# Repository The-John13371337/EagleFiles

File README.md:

# EagleFiles
This is a small Repo for cloning the malduino project files for the board design.
Seytonic didnt make this, i did because he refuses to upload the board schematics (although he is very busy)
Enjoy
Also btw im pretty sure that this board will work however look over the .sch and the sch preview so if somthing is wrong you can tell me and ill fix it.

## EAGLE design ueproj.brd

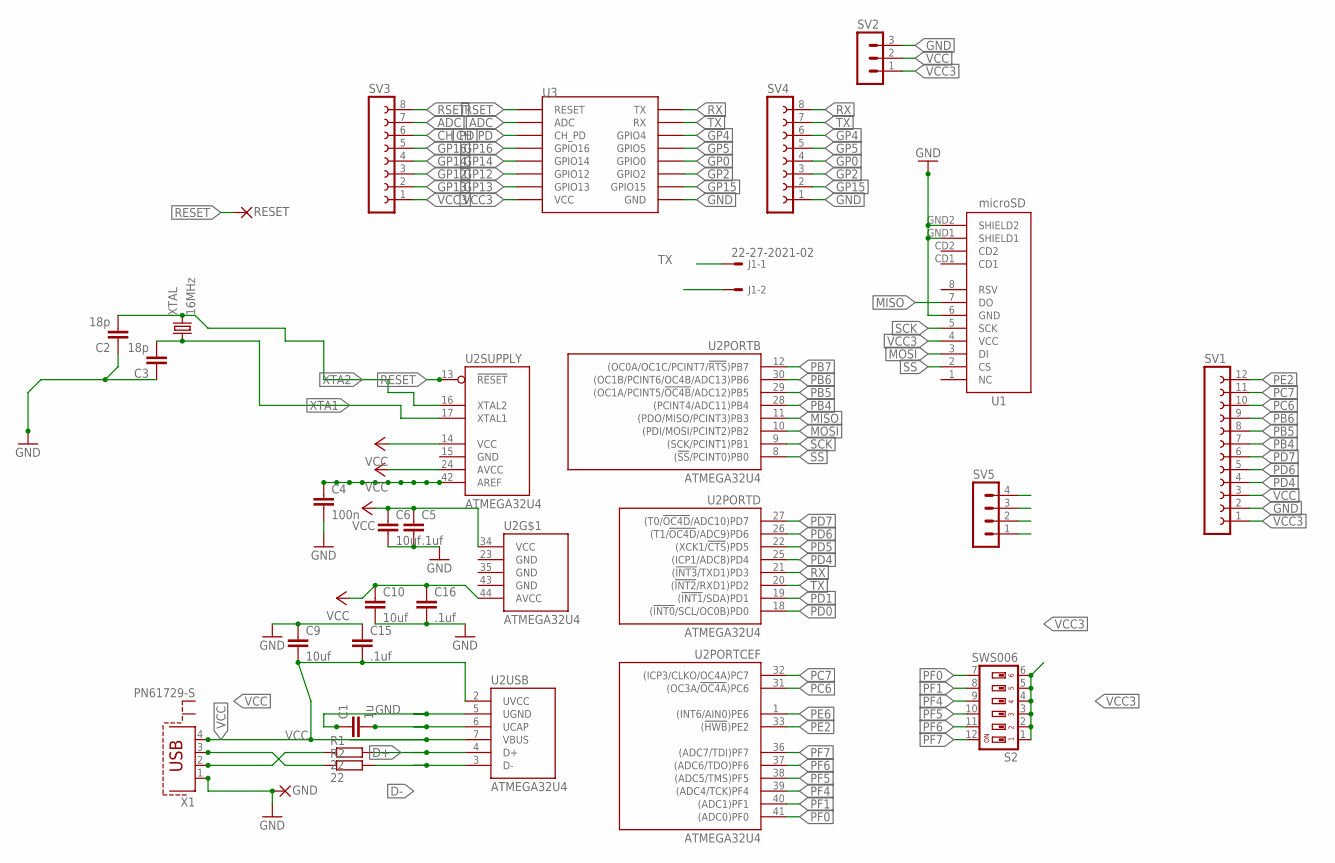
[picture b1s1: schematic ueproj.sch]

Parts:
C1: 1u; C0603
C2, C3: 18p; C0603
C4: 100n; C0603
C5, C15, C16: .1uf; C0603
C6, C10: 10uf; C2.5-2
C9: 10uf; C0603
GND: WIREPAD2,15/1,0-NOPLACE; 2,15/1,0-NOPLACE
J1: 22-27-2021-02; 6410-02
R1, R2: 22; R0603
RESET: WIREPAD2,15/1,0-NOPLACE; 2,15/1,0-NOPLACE
S2: SWS006; SMS-006
SV1: FE12-1; FE12
SV2: MA03-1
SV3, SV4: FE08-1; FE08
SV5: MA04-1
U1: microSD; MICRO-SD-SOCKET-PP
U2: ATMEGA32U4; TQFP44
U3: ESP12SMD; ESP12-SMD
X1: PN61729-S
XTAL: 16MHz; ABM7

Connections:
ADC: SV3.7, U3.ADC
AREF: C4.1, U2.42 (AREF)
CH_PD: SV3.6, U3.CH_PD
D+: R1.2, U2.4 (D+)
D-: R2.2, U2.3 (D-)
GND: C1.1, C2.1, C3.1, C4.2, C10.2, C16.2, GND.1, SV1.2, SV2.3, SV4.1, U1.6 (GND), U1.GND1 (SHIELD1), U1.GND2 (SHIELD2), U2.5 (UGND), U2.15 (GND), U2.23 (GND), U2.35 (GND), U2.43 (GND), U3.GND, X1.1
GP0: SV4.4, U3.GPIO0
GP2: SV4.3, U3.GPIO2
GP4: SV4.6, U3.GPIO4
GP5: SV4.5, U3.GPIO5
GP12: SV3.3, U3.GPIO12
GP13: SV3.2, U3.GPIO13
GP14: SV3.4, U3.GPIO14
GP15: SV4.2, U3.GPIO15
GP16: SV3.5, U3.GPIO16
MISO: SV5.4, U1.7 (DO), U2.11 ((PDO/MISO/PCINT3)PB3)
MOSI: SV5.2, U1.3 (DI), U2.10 ((PDI/MOSI/PCINT2)PB2)
unnamed: C9.1, C15.1
unnamed: C5.2, C6.2
unnamed: C1.2, U2.6 (UCAP)
unnamed: R1.1, X1.2
unnamed: R2.1, X1.3
PB4: SV1.7, U2.28 ((PCINT4/ADC11)PB4)
PB5: SV1.8, U2.29 ((OC1A/PCINT5/!OC4B!/ADC12)PB5)
PB6: SV1.9, U2.30 ((OC1B/PCINT6/OC4B/ADC13)PB6)
PB7: U2.12 ((OC0A/OC1C/PCINT7/!RTS!)PB7)
PC6: SV1.10, U2.31 ((OC3A/!OC4A!)PC6)
PC7: SV1.11, U2.32 ((ICP3/CLKO/OC4A)PC7)
PD0: U2.18 ((!INT0!/SCL/OC0B)PD0)
PD1: U2.19 ((!INT1!/SDA)PD1)
PD4: SV1.4, U2.25 ((ICP1/ADC8)PD4)
PD5: U2.22 ((XCK1/!CTS!)PD5)
PD6: SV1.5, U2.26 ((T1/!OC4D!/ADC9)PD6)
PD7: SV1.6, U2.27 ((T0/!OC4D!/ADC10)PD7)
PE2: SV1.12, U2.33 ((!HWB!)PE2)
PE6: U2.1 ((INT6/AIN0)PE6)
PF0: S2.7, U2.41 ((ADC0)PF0)
PF1: S2.8, U2.40 ((ADC1)PF1)
PF4: S2.9, U2.39 ((ADC4/TCK)PF4)
PF5: S2.10, U2.38 ((ADC5/TMS)PF5)
PF6: S2.11, U2.37 ((ADC6/TDO)PF6)
PF7: S2.12, U2.36 ((ADC7/TDI)PF7)
RESET: RESET.1, U2.13 (!RESET)
RSET: SV3.8, U3.RESET
RX: J1.2, SV4.8, U2.21 ((!INT3!/TXD1)PD3), U3.TXD0 (TX)
SCK: SV5.3, U1.5 (SCK), U2.9 ((SCK/PCINT1)PB1)
SS: SV5.1, U1.2 (CS), U2.8 ((!SS!/PCINT0)PB0)
TX: J1.1, SV4.7, U2.20 ((!INT2!/RXD1)PD2), U3.RXD0 (RX)
VCC: C5.1, C6.1, C9.2, C10.1, C15.2, C16.1, SV1.3, SV2.2, U2.2 (UVCC), U2.7 (VBUS), U2.14 (VCC), U2.24 (AVCC), U2.34 (VCC), U2.44 (AVCC), X1.4
VCC3: S2.1, S2.2, S2.3, S2.4, S2.5, S2.6, SV1.1, SV2.1, SV3.1, U1.4 (VCC), U3.VCC
XTA1: C3.2, U2.17 (XTAL1), XTAL.P$1 (1)
XTA2: C2.2, U2.16 (XTAL2), XTAL.P$2 (2)

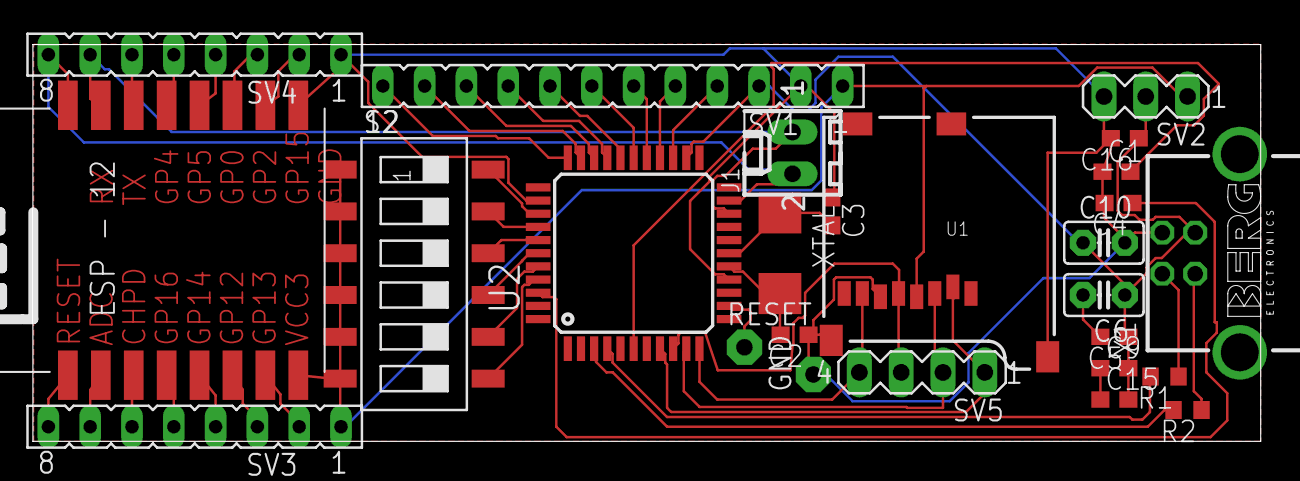
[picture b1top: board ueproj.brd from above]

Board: 2 copper layers, 74.6 x 24.1 mm, 26 parts (0 on the bottom side), 47 nets.

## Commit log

2017-07-03 Update README.md
    Updated the Readmeme file to include insurance policy
